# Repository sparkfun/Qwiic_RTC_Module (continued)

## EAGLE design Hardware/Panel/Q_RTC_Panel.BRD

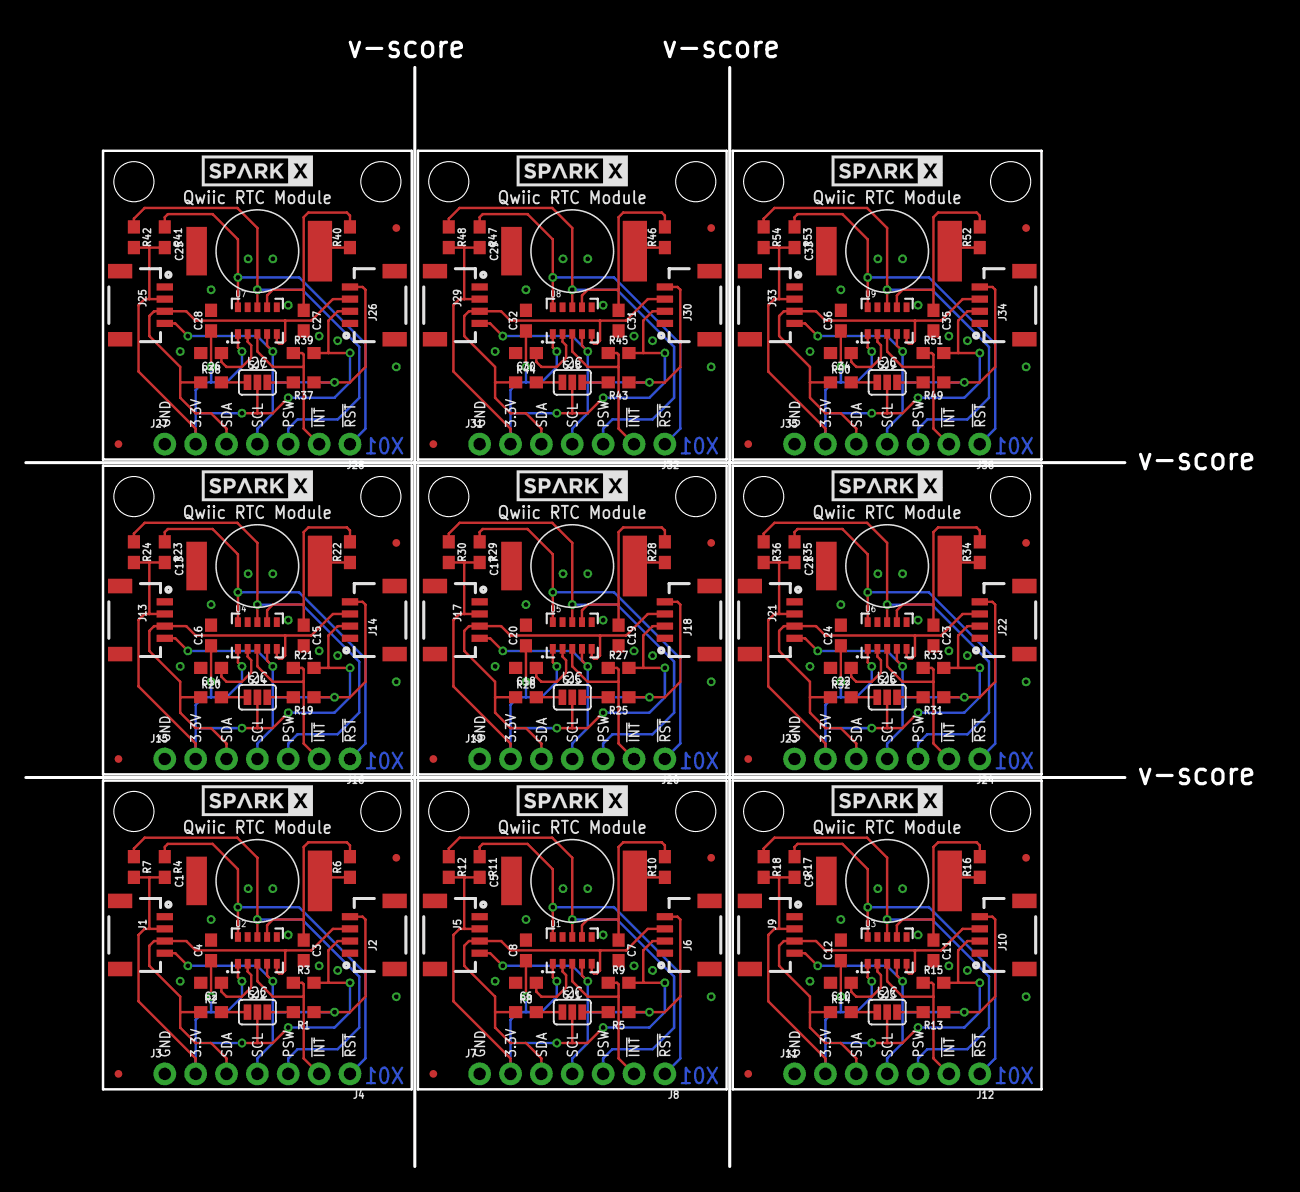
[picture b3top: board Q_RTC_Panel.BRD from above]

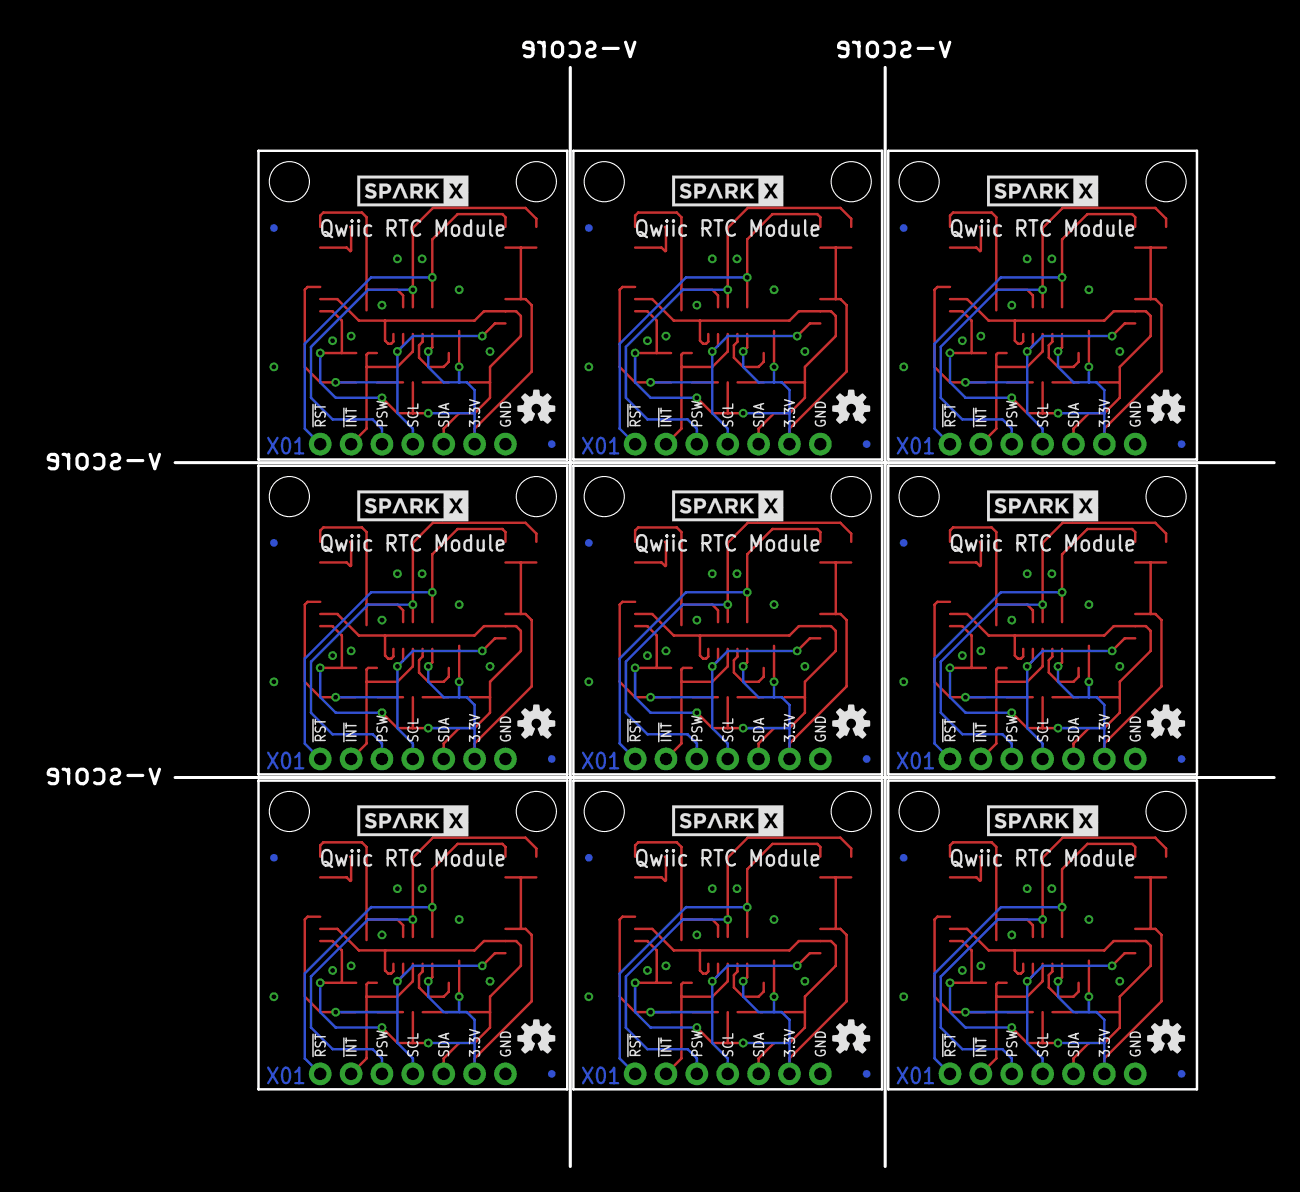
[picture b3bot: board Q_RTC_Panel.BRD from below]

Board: 2 copper layers, 90.4 x 90.4 mm, 225 parts (36 on the bottom side), 108 nets.

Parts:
C1, C5, C9, C13, C17, C21, C25, C29, C33: .22F-SUPERCAP; DSK-RADIAL-6.8MM
C2, C6, C10, C14, C18, C22, C26, C30, C34: 47pF; 0603
C3, C4, C7, C8, C11, C12, C15, C16, C19, C20, C23, C24, C27, C28, C31, C32, C35, C36: 10nF; 0603
FD1, FD2, FD3, FD4, FD5, FD6, FD7, FD8, FD9, FD10, FD11, FD12, FD13, FD14, FD15, FD16, FD17, FD18, FD19, FD20, FD21, FD22, FD23, FD24, FD25, FD26, FD27, FD28, FD29, FD30, FD31, FD32, FD33, FD34, FD35, FD36: FIDUCIALUFIDUCIAL; FIDUCIAL-MICRO
J1, J2, J5, J6, J9, J10, J13, J14, J17, J18, J21, J22, J25, J26, J29, J30, J33, J34: SMD; 1X04_1MM_RA
J3, J7, J11, J15, J19, J23, J27, J31, J35: PTH; 1X04_NO_SILK
J4, J8, J12, J16, J20, J24, J28, J32, J36: 1X03_NO_SILK
LOGO1, LOGO2, LOGO3, LOGO4, LOGO5, LOGO6, LOGO7, LOGO8, LOGO9: OSHW-LOGOS; OSHW-LOGO-S
R1, R2, R5, R8, R13, R14, R19, R20, R25, R26, R31, R32, R37, R38, R43, R44, R49, R50: 2.2k; 0603
R3, R4, R7, R9, R11, R12, R15, R17, R18, R21, R23, R24, R27, R29, R30, R33, R35, R36, R39, R41, R42, R45, R47, R48, R51, R53, R54: 10k; 0603
R6, R10, R16, R22, R28, R34, R40, R46, R52: 1K; 0603
SJ1, SJ2, SJ3, SJ4, SJ5, SJ6, SJ7, SJ8, SJ9: JUMPER-SMT_3_2-NC_PASTE_SILK; SMT-JUMPER_3_2-NC_PASTE_SILK
U1, U2, U3, U4, U5, U6, U7, U8, U9: RV-1805
U$1, U$2, U$6, U$7, U$9, U$10, U$13, U$14, U$17, U$18, U$21, U$22, U$25, U$26, U$29, U$30, U$33, U$34: STAND-OFF
U$3, U$4, U$5, U$8, U$11, U$12, U$15, U$16, U$19, U$20, U$23, U$24, U$27, U$28, U$31, U$32, U$35, U$36: SPARKX-LOGO4; SPARKX-MEDIUM

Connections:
3.3V: C4.1, J1.2, J2.2, J3.2, R3.2, R4.2, R7.2, SJ2.2, U2.1
3.3V1: C8.1, J5.2, J6.2, J7.2, R9.2, R11.2, R12.2, SJ1.2, U1.1
3.3V2: C12.1, J9.2, J10.2, J11.2, R15.2, R17.2, R18.2, SJ3.2, U3.1
3.3V3: C16.1, J13.2, J14.2, J15.2, R21.2, R23.2, R24.2, SJ4.2, U4.1
3.3V4: C20.1, J17.2, J18.2, J19.2, R27.2, R29.2, R30.2, SJ5.2, U5.1
3.3V5: C24.1, J21.2, J22.2, J23.2, R33.2, R35.2, R36.2, SJ6.2, U6.1
3.3V6: C28.1, J25.2, J26.2, J27.2, R39.2, R41.2, R42.2, SJ7.2, U7.1
3.3V7: C32.1, J29.2, J30.2, J31.2, R45.2, R47.2, R48.2, SJ8.2, U8.1
3.3V8: C36.1, J33.2, J34.2, J35.2, R51.2, R53.2, R54.2, SJ9.2, U9.1
!INT: J4.2, R3.1, U2.3
!INT1: J8.2, R9.1, U1.3
!INT2: J12.2, R15.1, U3.3
!INT3: J16.2, R21.1, U4.3
!INT4: J20.2, R27.1, U5.3
!INT5: J24.2, R33.1, U6.3
!INT6: J28.2, R39.1, U7.3
!INT7: J32.2, R45.1, U8.3
!INT8: J36.2, R51.1, U9.3
!RST: J4.1, R4.1, U2.10
!RST1: J8.1, R11.1, U1.10
!RST2: J12.1, R17.1, U3.10
!RST3: J16.1, R23.1, U4.10
!RST4: J20.1, R29.1, U5.10
!RST5: J24.1, R35.1, U6.10
!RST6: J28.1, R41.1, U7.10
!RST7: J32.1, R47.1, U8.10
!RST8: J36.1, R53.1, U9.10
GND: C1.-, C2.2, C3.2, C4.2, J1.1, J2.1, J3.1, U2.6, U2.9
GND1: C5.-, C6.2, C7.2, C8.2, J5.1, J6.1, J7.1, U1.6, U1.9
GND2: C9.-, C10.2, C11.2, C12.2, J9.1, J10.1, J11.1, U3.6, U3.9
GND3: C13.-, C14.2, C15.2, C16.2, J13.1, J14.1, J15.1, U4.6, U4.9
GND4: C17.-, C18.2, C19.2, C20.2, J17.1, J18.1, J19.1, U5.6, U5.9
GND5: C21.-, C22.2, C23.2, C24.2, J21.1, J22.1, J23.1, U6.6, U6.9
GND6: C25.-, C26.2, C27.2, C28.2, J25.1, J26.1, J27.1, U7.6, U7.9
GND7: C29.-, C30.2, C31.2, C32.2, J29.1, J30.1, J31.1, U8.6, U8.9
GND8: C33.-, C34.2, C35.2, C36.2, J33.1, J34.1, J35.1, U9.6, U9.9
unnamed: R1.2, SJ2.3
unnamed: R2.2, SJ2.1
unnamed: R5.2, SJ1.3
unnamed: C2.1, U2.2
unnamed: C1.+, R6.1
unnamed: R8.2, SJ1.1
unnamed: C6.1, U1.2
unnamed: C5.+, R10.1
unnamed: R13.2, SJ3.3
unnamed: R14.2, SJ3.1
unnamed: C10.1, U3.2
unnamed: C9.+, R16.1
unnamed: R19.2, SJ4.3
unnamed: R20.2, SJ4.1
unnamed: C14.1, U4.2
unnamed: C13.+, R22.1
unnamed: R25.2, SJ5.3
unnamed: R26.2, SJ5.1
unnamed: C18.1, U5.2
unnamed: C17.+, R28.1
unnamed: R31.2, SJ6.3
unnamed: R32.2, SJ6.1
unnamed: C22.1, U6.2
unnamed: C21.+, R34.1
unnamed: R37.2, SJ7.3
unnamed: R38.2, SJ7.1
unnamed: C26.1, U7.2
unnamed: C25.+, R40.1
unnamed: R43.2, SJ8.3
unnamed: R44.2, SJ8.1
unnamed: C30.1, U8.2
unnamed: C29.+, R46.1
unnamed: R49.2, SJ9.3
unnamed: R50.2, SJ9.1
unnamed: C34.1, U9.2
unnamed: C33.+, R52.1
PSW: J4.3, R7.1, U2.8
PSW1: J8.3, R12.1, U1.8
PSW2: J12.3, R18.1, U3.8
PSW3: J16.3, R24.1, U4.8
PSW4: J20.3, R30.1, U5.8
PSW5: J24.3, R36.1, U6.8
PSW6: J28.3, R42.1, U7.8
PSW7: J32.3, R48.1, U8.8
PSW8: J36.3, R54.1, U9.8
SCL: J1.4, J2.4, J3.4, R1.1, U2.4
SCL1: J5.4, J6.4, J7.4, R5.1, U1.4
SCL2: J9.4, J10.4, J11.4, R13.1, U3.4
SCL3: J13.4, J14.4, J15.4, R19.1, U4.4
SCL4: J17.4, J18.4, J19.4, R25.1, U5.4
SCL5: J21.4, J22.4, J23.4, R31.1, U6.4
SCL6: J25.4, J26.4, J27.4, R37.1, U7.4
SCL7: J29.4, J30.4, J31.4, R43.1, U8.4
SCL8: J33.4, J34.4, J35.4, R49.1, U9.4
SDA: J1.3, J2.3, J3.3, R2.1, U2.5
SDA1: J5.3, J6.3, J7.3, R8.1, U1.5
SDA2: J9.3, J10.3, J11.3, R14.1, U3.5
SDA3: J13.3, J14.3, J15.3, R20.1, U4.5
SDA4: J17.3, J18.3, J19.3, R26.1, U5.5
SDA5: J21.3, J22.3, J23.3, R32.1, U6.5
SDA6: J25.3, J26.3, J27.3, R38.1, U7.5
SDA7: J29.3, J30.3, J31.3, R44.1, U8.5
SDA8: J33.3, J34.3, J35.3, R50.1, U9.5
VBACKUP: C3.1, R6.2, U2.7
VBACKUP1: C7.1, R10.2, U1.7
VBACKUP2: C11.1, R16.2, U3.7
VBACKUP3: C15.1, R22.2, U4.7
VBACKUP4: C19.1, R28.2, U5.7
VBACKUP5: C23.1, R34.2, U6.7
VBACKUP6: C27.1, R40.2, U7.7
VBACKUP7: C31.1, R46.2, U8.7
VBACKUP8: C35.1, R52.2, U9.7

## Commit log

2017-12-13 Board ready for design review
2017-12-21 post design review changes
2017-12-27 fixed checklist issues
2018-01-24 updated sensor
2018-01-25 Updated RTC module
2018-01-31 updated to RV-1805
2018-01-31 updated cap value
2018-02-01 Updated cap footprint, broke out rest of pins
2018-02-02 Moved via
2018-02-02 Changed pull ups, super cap silk, added panel.
    Removed dupicate resistor on super cap. Removed pin 1 silk on super cap. Change I2C pull ups to 2.2k for 3.3V devices. Changed pull ups to 10k for lower draw. Added panel.
2018-02-09 laying out with battery
2018-02-12 added battery footprint, went through engineering checklist
2018-02-14 post review changes
2018-02-15 Qwiic RTC silk change
2018-02-28 order protos, fix resistor PROD_ID
2018-03-07 post checklist changes
2018-03-12 updated battery package
2018-03-12 created panel v10
2018-05-31 cleaning up library for release
